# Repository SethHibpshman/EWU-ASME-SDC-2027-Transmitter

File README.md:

# EWU ASME SDC 2027 Transmitter

> A custom handheld Operator Console for the EWU ASME chapter's 2027 ASME Student Design Competition robot, built around an ESP32-S3 on a custom PCB and talking to the robot over ESP-NOW. **Work in progress.**

> This repo covers only the transmitter. The competition rules, playfield models, and the robot itself are in the main repo: [EWU-ASME-SDC-2027-Robot](https://github.com/SethHibpshman/EWU-ASME-SDC-2027-Robot).

## Table of Contents

- [Overview](#overview)
- [Status](#status)
- [Functionality](#functionality)
- [System Design](#system-design)
- [Bill of Materials](#bill-of-materials)
- [Author](#author)
- [AI Disclosure](#ai-disclosure)
- [License](#license)

## Overview

The 2027 ASME Student Design Competition (eFest SDC), PODIUM, has one robot compete in five Disciplines. Each Run starts with a 30-second autonomous phase and ends with a 2-minute crewed phase, where the team drives the robot through its own Operator Console. The rules allow exactly one control link on a license-free band, the robot must be able to be disabled from the remote, and any battery in the remote must be a commercially made cell.

Instead of reusing the hobby RC radio from the [2026 robot](https://github.com/SethHibpshman/EWU-ASME-SDC-2026-Robot), this project is a purpose-built controller: an ESP32-S3 dev board on a custom PCB with joysticks, potentiometers, buttons, a display, and its own rechargeable battery system. Reliability comes first, followed by learning C/C++, building transferable skills, and a clean-looking design.

## Status

| Stage | State |
|---|---|
| Rev A PCB | Designed for JLCPCB assembly, not built (over $100 for two units) |
| Rev B PCB | Ordered, hand-assembled, and tested |
| Firmware | Not started |

## Functionality

### Inputs and Feedback

The layout follows a typical RC transmitter: two joysticks, two potentiometers, and eight buttons in two diamond clusters of four.

| Feature | Part |
|---|---|
| **Microcontroller** | ESP32-S3-DevKitC-1 N16R8 (dual USB-C) in female headers |
| **Drive inputs** | 2x 2-axis analog joysticks (YF16-FL7.2-B5KA, 5 kΩ) |
| **Proportional inputs** | 2x rotary potentiometers (RK09K1130AAU, 10 kΩ) |
| **Buttons** | 8x 12 mm action buttons and a power button |
| **Display** | 128x64 I2C OLED (HS13L03W2C01) |
| **Status lights** | 5 mm center LED and the devkit's built-in LED |
| **Expansion** | 2x5 header for spare GPIO |
| **Mounting** | 4 grounded M3 holes, one in each corner |

### Wireless Link

The transmitter uses ESP-NOW on 2.4 GHz, Espressif's connectionless peer-to-peer protocol. It needs no router, has millisecond-level latency, and gives two-way telemetry between the robot and the transmitter.

| Radio | Rough Range | Needs Infrastructure? | Power | Best For |
|---|---|---|---|---|
| Wi-Fi | Tens of metres | Router plus internet | Moderate to high | Dashboards, apps, cloud |
| **ESP-NOW** | Similar to Wi-Fi, more outdoors | None | Low | Board-to-board messaging |
| LoRa | Hundreds of metres to kilometres | LoRa module, gateway for LoRaWAN | Very low | Remote, sparse sensors |

LoRa's range isn't needed for a pilot a few metres from the board, and its small packets limit how fast data can be sent. Wi-Fi needs a router.

### Power

| Feature | Part |
|---|---|
| **Battery** | Single Li-ion cell |
| **Charger and 5 V boost** | IP5306-I2C |
| **Battery protection** | IP3005A, with a bypass jumper (R20) |
| **USB ESD protection** | USBLC6-2SC6 |
| **Backfeed blocking** | SS34 Schottky on the boost output |
| **Soft shutdown** | 2N7000 on the IP5306 KEY pin, driven by the MCU |
| **Fuel gauge** | 100 kΩ / 100 kΩ divider to an ADC pin |

The I2C version of the IP5306 was chosen so the MCU can turn off its auto-shutoff, which would otherwise cut power after 30 seconds of low current draw. Over I2C the MCU can also read charging state and battery level.

## System Design

### Hardware

The back of the board carries the author's maker's mark, the board name, date and revision, and the EWU insignia for the team behind the eFest project.

Designed in KiCad 10 as a two-sheet schematic: the [main sheet](/assets/schematic/schematic_main.svg) (ESP32-S3, inputs, display, and expansion header) and a [Battery Charging & Protection sheet](/assets/schematic/schematic_power.svg). All project files are in [`/hardware/kicad_project_files`](/hardware/kicad_project_files).

#### ESP32-S3 Development Board

- 100 nF and 10 µF capacitors on the 3V3 rail: the 100 nF handles fast logic switching spikes, the 10 µF covers radio transmit bursts (~250 mA) before the regulator catches up.
- 100 nF on each analog input forms an RC low-pass filter with the pot or joystick (cutoff ~637 Hz for the 10 kΩ pots, ~1.27 kHz for the 5 kΩ joysticks). User input passes through; the IP5306's ~500 kHz switching noise and 2.4 GHz radio noise are blocked.

#### Battery and Power Management

USB data and VIN pass through the USBLC6-2SC6 ESD protection IC. The USB+ and USB- traces are routed together at matched length.

The IP5306 circuit follows the manufacturer's I2C application schematic, with these changes:

- I2C pulled up to 3V3 instead of BATT+ to protect the MCU
- 100 kΩ / 100 kΩ fuel-gauge divider for a finer battery reading
- SS34 Schottky on VOUT to block backfeed when the devkit is on USB power
- 2N7000 on the KEY pin so the MCU can force a shutdown
- Flashlight LED removed and the exposed pad grounded
- INT routed through a jumper (R5) so its voltage can be checked before it reaches a GPIO

The IP3005A battery protection IC is set up as the manufacturer recommends, with an optional jumper (R20) from BAT- to Pack- to bypass it.

#### User Input and Feedback

The joysticks and pots run from 3V3 to GND. Buttons connect a GPIO to GND, with pull-ups handled in firmware.

#### Exposed Pins

Spare usable GPIO is broken out to a 2x5 header for future expansion.

#### PCB

| Property | Value |
|---|---|
| Size | 150 x 110 x 1.6 mm, 2 layers |
| Routing | Back copper vertical, front copper horizontal |
| 1 mm traces | +P, BAT-, VIN, SW, VOUT |
| 0.5 mm traces | +5V, +3V3 |
| 0.2 mm traces | Signals |
| Ground | Poured on both layers, stitched with vias every 5 mm (under λ/10 at 2.4 GHz) |
| Finishing | Islands removed, teardrops added |

#### Rev A to Rev B

Rev B was a cost-cutting revision, going from over $100 to about $50 for two transmitters (about $25 each).

- Dropped JLCPCB assembly. The board is now hand-soldered in-house.
- Swapped 0603 passives for 0805 and gave hard-to-reach parts (like the inductor) hand-solder footprints.
- Replaced the SMD USB-C port with a 1x4 header (VIN, GND, USB+, USB-) wired to the ESP32-S3's native USB, so a USB-C module can be added later.
- Added labeled test pads (VIN, +P, BAT-, 3V3, 5V0, INT, fuel gauge, IO8) and back-side silkscreen.

#### Assembly and Bring-Up

Assembly took about two hours, plus two hours of testing. SMD parts went on first, then through-hole. The devkit sits in female headers, so it stayed off the board while the power section was tested from a 3.7 V bench supply.

| Fault | Cause | Fix |
|---|---|---|
| Boost output 2 V instead of 5 V | IP5306 exposed pad not soldered to ground | Reflowed the pad from the back through the via with flux |
| No USB device through J2 | USB+ open between USBLC6 and GPIO20 | Resoldered the USBLC6 |

With both fixed, the boost reads 5 V, a cell charges from 4.0 V to 4.2 V on USB, and the board enumerates through J2. The battery protection IC was out of stock, so it was left off and bypassed with R20.

### Software

Firmware will be C++ on the Arduino-ESP32 core. As a fail-safe, the robot stops all operations if it stops receiving packets from the transmitter.

```
EWU-ASME-SDC-2027-Transmitter/
├── assets/
│   ├── pcb_render_front.png                     # 3D render of the PCB, front
│   ├── pcb_render_back.jpg                      # 3D render of the PCB, back
│   ├── pcb_assembled.jpg                        # Photo of the assembled Rev B board
│   └── schematic/                               # Schematic sheets (SVG) and section images
└── hardware/
    ├── kicad_project_files/
    │   ├── transmitter.kicad_pro                # KiCad project
    │   ├── transmitter.kicad_sch                # Main schematic sheet
    │   ├── Battery Charging & Protection.kicad_sch
    │   └── transmitter.kicad_pcb                # PCB layout
    └── fabrication/                             # JLCPCB outputs
        ├── gerber/                              # Gerbers and drill files
        └── production_files/                    # BOM, CPL, and Gerber zip
```

## Bill of Materials

The full BOM with LCSC part numbers is in [`BOM-transmitter.csv`](/hardware/fabrication/production_files/BOM-transmitter.csv). Rev B costs about $25 per transmitter, with a minimum PCB order of 5.

## Author

**Seth Hibpshman**  
Student of Electrical Engineering, Eastern Washington University

## AI Disclosure
_AI (LLM) tools were used in the drafting and editing of this README._

## License

[GNU General Public License v3.0](LICENSE)

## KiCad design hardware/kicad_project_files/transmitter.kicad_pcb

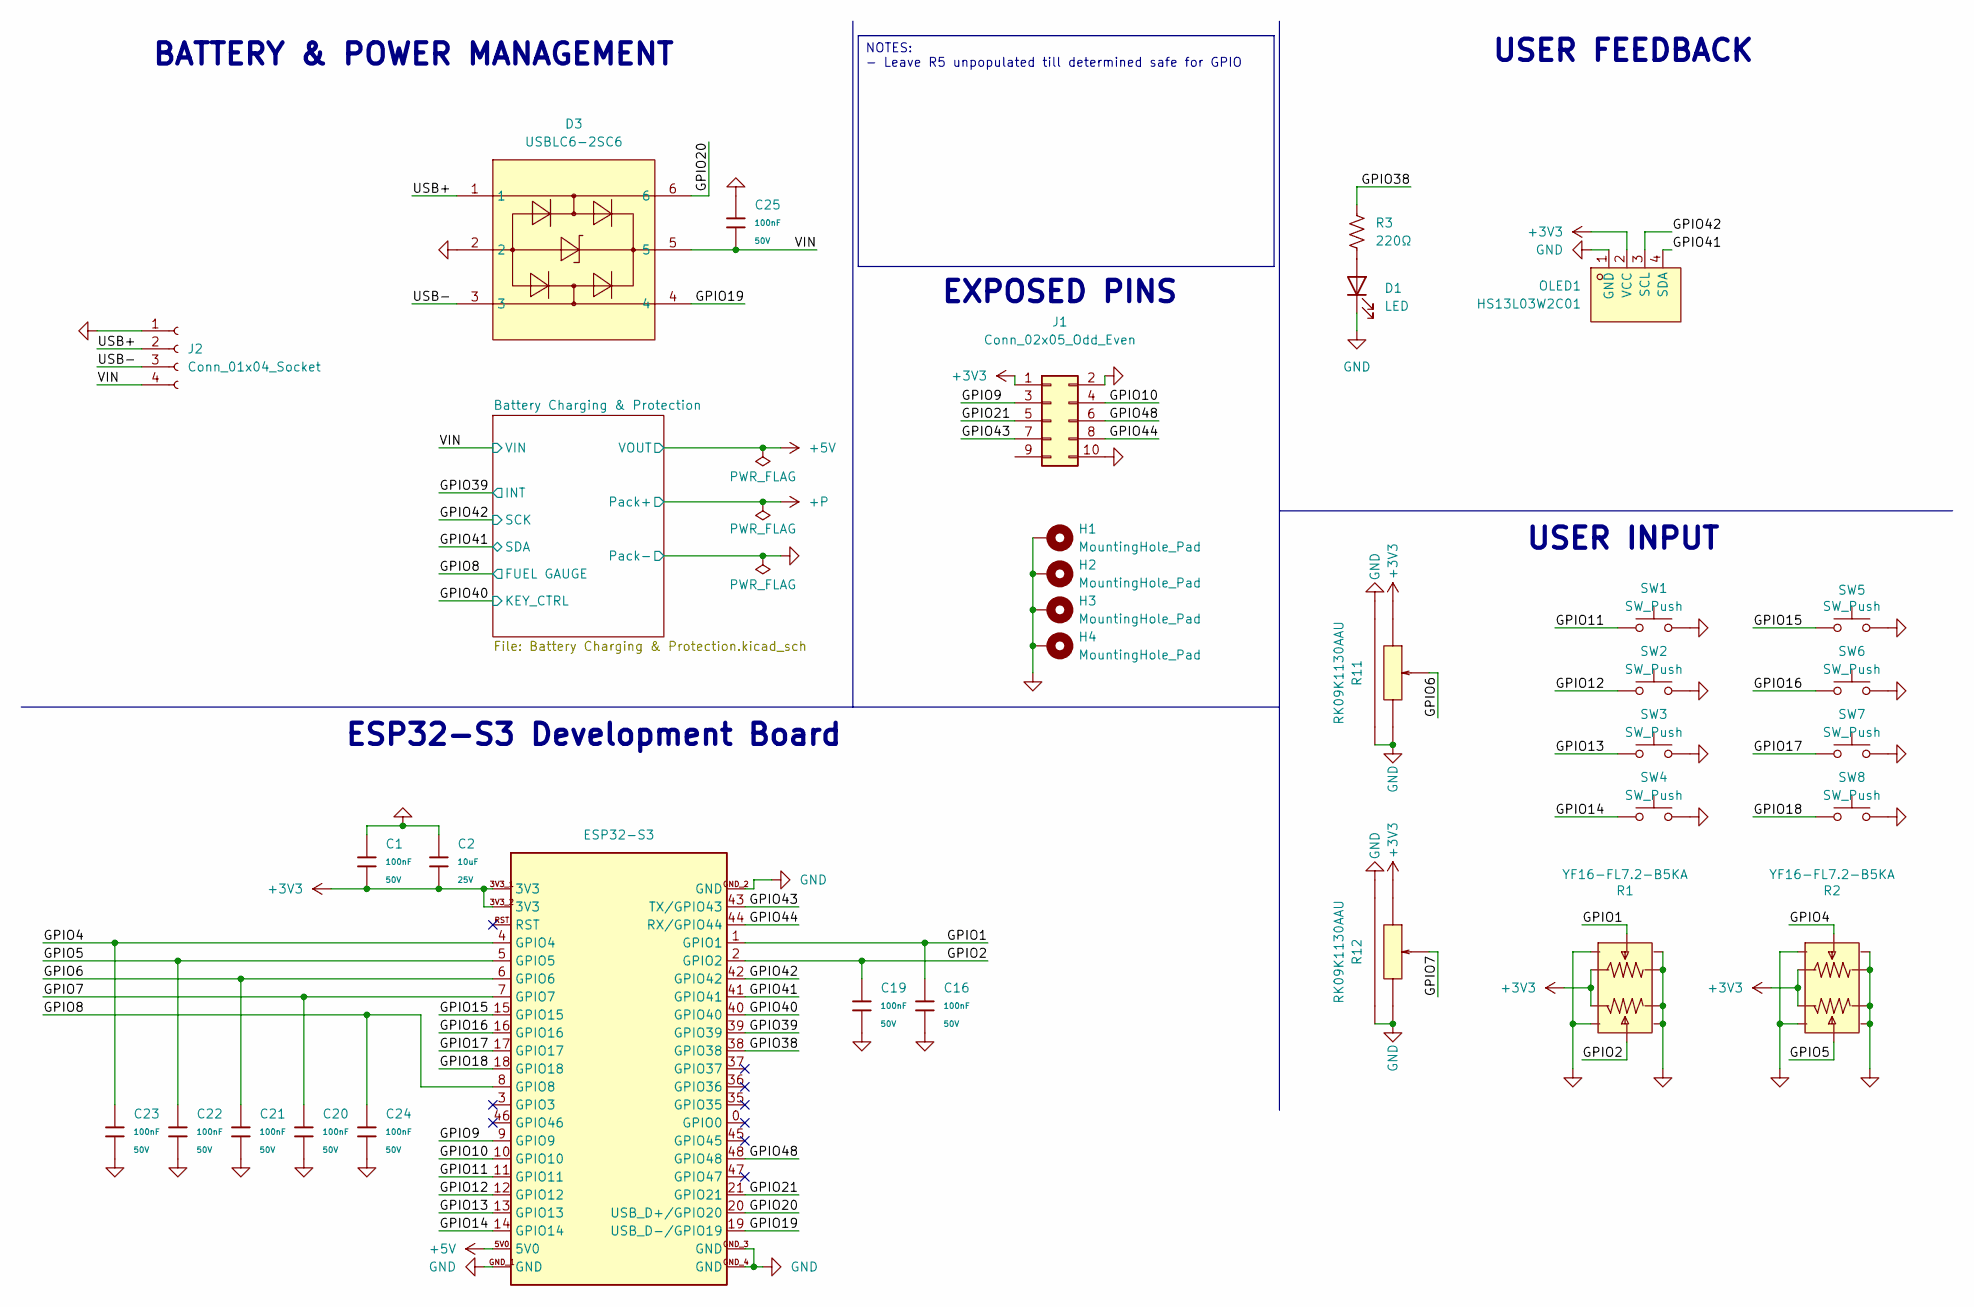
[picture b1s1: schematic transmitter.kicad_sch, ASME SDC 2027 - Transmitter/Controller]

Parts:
C1, C16, C19, C20, C21, C22, C23, C24, C25: 100nF; C_0805; Voltage Rated 50V; Tolerance ±10%; Part CC0603KRX7R9BB104; LCSC C14663
C2: 10uF; C_0805; Voltage Rated 25V; Tolerance ±20%; Part CL10A106MA8NRNC; LCSC C96446
D1: LED; LED_D5.0mm
D3: USBLC6-2SC6; SOT-23-6_L2.9-W1.6-P0.95-LS2.8-BL; MPN USBLC6-2SC6; LCSC Part C7519
ESP32-S3: Devboard_ESP32-S3_N16R8_DualUSB-C_YELUFT
H1, H2, H3, H4: MountingHole_Pad; MountingHole_3mm_Pad_Via
J1: Conn_02x05_Odd_Even; PinSocket_2x05_P2.54mm_Vertical
J2: Conn_01x04_Socket; PinHeader_1x04_P2.54mm_Vertical
OLED1: HS13L03W2C01; OLED-TH_L35.4-W33.5_HS13L03W2C01; MPN HS13L03W2C01; LCSC Part C7465997
R1, R2: YF16-FL7.2-B5KA; JOYTICK-TH_YF16-DFL7.2-B5KO-45-10-B5KO-55--RG-A22; MPN YF16-FL7.2-B5Ka(45-10)-R-A28; LCSC Part C37323739
R3: 220Ω; R_0805
R11, R12: RK09K1130AAU; RES-TH_RK09K1130AAU; MPN RK09K1130AAU; LCSC Part C202373
SW1, SW2, SW3, SW4, SW5, SW6, SW7, SW8: SW_Push; SW_PUSH-12mm_Wuerth-430476085716

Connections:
+3V3: C1.2, C2.2, ESP32-S3.3V3_1 (3V3), ESP32-S3.3V3_2 (3V3), J1.1, OLED1.2 (VCC), R1.3, R1.6, R2.3, R2.6, R11.3, R12.3; also elsewhere on the board
+5V: ESP32-S3.5V0; also elsewhere on the board
/GPIO1: C16.1, ESP32-S3.1 (GPIO1), R1.2
/GPIO2: C19.1, ESP32-S3.2 (GPIO2), R1.5
/GPIO4: C23.1, ESP32-S3.4 (GPIO4), R2.2
/GPIO5: C22.1, ESP32-S3.5 (GPIO5), R2.5
/GPIO6: C21.1, ESP32-S3.6 (GPIO6), R11.2
/GPIO7: C20.1, ESP32-S3.7 (GPIO7), R12.2
/GPIO8: C24.1, ESP32-S3.8 (GPIO8); also elsewhere on the board
/GPIO9: ESP32-S3.9 (GPIO9), J1.3
/GPIO10: ESP32-S3.10 (GPIO10), J1.4
/GPIO11: ESP32-S3.11 (GPIO11), SW1.1
/GPIO12: ESP32-S3.12 (GPIO12), SW2.1
/GPIO13: ESP32-S3.13 (GPIO13), SW3.1
/GPIO14: ESP32-S3.14 (GPIO14), SW4.1
/GPIO15: ESP32-S3.15 (GPIO15), SW5.1
/GPIO16: ESP32-S3.16 (GPIO16), SW6.1
/GPIO17: ESP32-S3.17 (GPIO17), SW7.1
/GPIO18: ESP32-S3.18 (GPIO18), SW8.1
/GPIO19: D3.4, ESP32-S3.19 (USB_D-/GPIO19)
/GPIO20: D3.6, ESP32-S3.20 (USB_D+/GPIO20)
/GPIO21: ESP32-S3.21 (GPIO21), J1.5
/GPIO38: ESP32-S3.38 (GPIO38), R3.1
/GPIO39: ESP32-S3.39 (GPIO39); also elsewhere on the board
/GPIO40: ESP32-S3.40 (GPIO40); also elsewhere on the board
/GPIO41: ESP32-S3.41 (GPIO41), OLED1.4 (SDA); also elsewhere on the board
/GPIO42: ESP32-S3.42 (GPIO42), OLED1.3 (SCL); also elsewhere on the board
/GPIO43: ESP32-S3.43 (TX/GPIO43), J1.7
/GPIO44: ESP32-S3.44 (RX/GPIO44), J1.8
/GPIO48: ESP32-S3.48 (GPIO48), J1.6
/USB+: D3.1, J2.2
/USB-: D3.3, J2.3
/VIN: C25.2, D3.5, J2.4; also elsewhere on the board
GND: C1.1, C2.1, C16.2, C19.2, C20.2, C21.2, C22.2, C23.2, C24.2, C25.1, D1.1 (K), D3.2, ESP32-S3.GND_1 (GND), ESP32-S3.GND_2 (GND), ESP32-S3.GND_3 (GND), ESP32-S3.GND_4 (GND), H1.1 (1_1), H2.1 (1_1), H3.1 (1_1), H4.1 (1_1), J1.2, J1.10, J2.1, OLED1.1 (GND), R1.1, R1.4, R1.7 (shell), R1.8 (shell), R1.9 (shell), R1.10 (shell), R2.1, R2.4, R2.7 (shell), R2.8 (shell), R2.9 (shell), R2.10 (shell), R11.1, R11.4 (EH), R11.5 (EH), R12.1, R12.4 (EH), R12.5 (EH), SW1.2, SW2.2, SW3.2, SW4.2, SW5.2, SW6.2, SW7.2, SW8.2; also elsewhere on the board
unnamed: D1.2 (A), R3.2

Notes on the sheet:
BATTERY & POWER MANAGEMENT
USER FEEDBACK
ESP32-S3 Development Board
USER INPUT
EXPOSED PINS
NOTES: - Leave R5 unpopulated till determined safe for GPIO

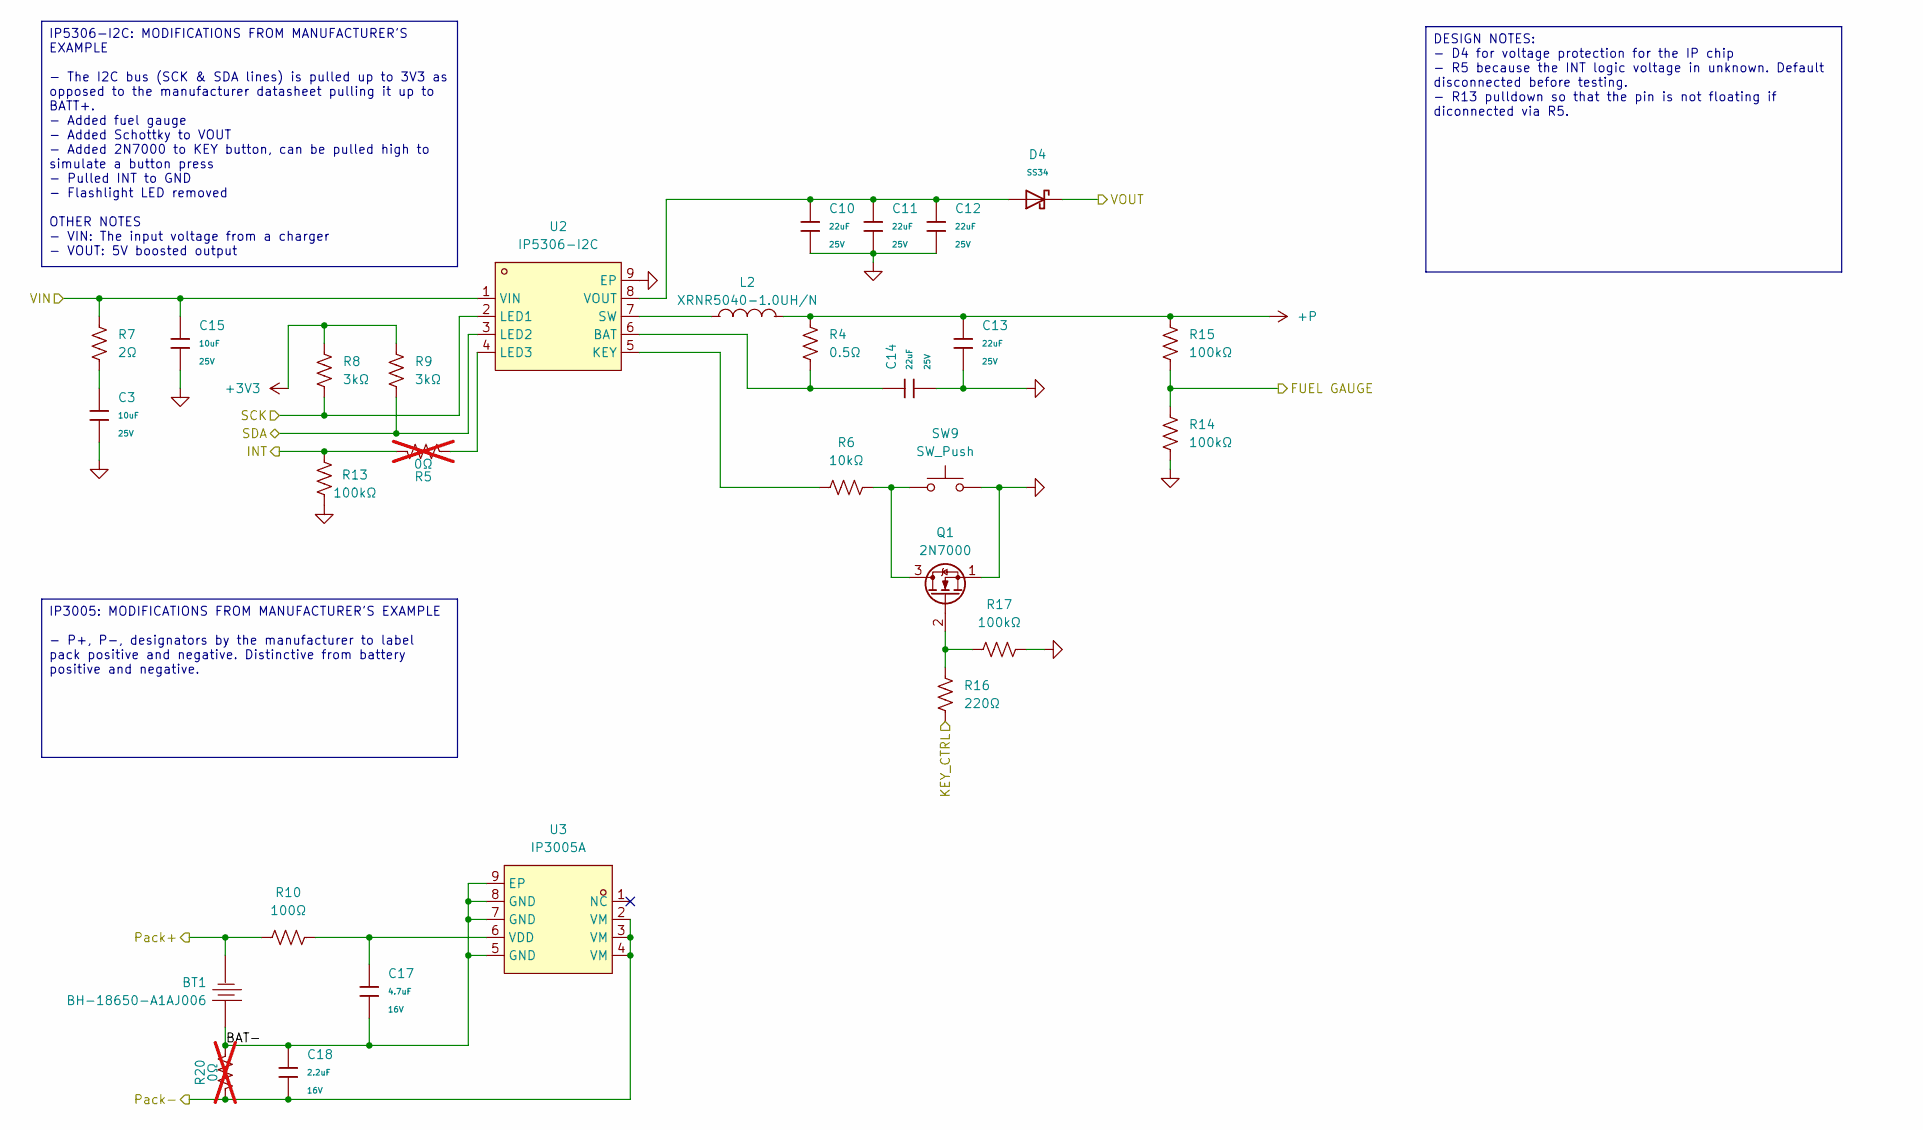
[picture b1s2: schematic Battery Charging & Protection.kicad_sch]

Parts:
BT1: BH-18650-A1AJ006; PinHeader_1x02_P2.54mm_Vertical; MPN BH-18650-A1AJ006; LCSC Part C5290175
C3, C15: 10uF; C_0805; Voltage Rated 25V; Tolerance ±20%; Part CL10A106MA8NRNC; LCSC C96446
C10, C11, C12, C13, C14: 22uF; C_0805; Voltage Rated 25V; Tolerance ±20%; Part CL21A226MAQNNNE; LCSC C45783
C17: 4.7uF; C_0805; Voltage Rated 16V; Tolerance ±10%; Part CL10A475KO8NNNC; LCSC C19666
C18: 2.2uF; C_0805; Voltage Rated 16V; Tolerance ±10%; Part CL10A225KO8NNNC; LCSC C23630
D4: SS34; D_SMA; Forward Voltage (Vf@If) 550mV@3A; Reverse Voltage (Vr) 40V; Part SS34; LCSC C8678
L2: XRNR5040-1.0UH/N; L_Taiyo-Yuden_NR-50xx_HandSoldering; MPN XRNR5040-1.0uH/N; LCSC Part C5339700
Q1: 2N7000; TO-92_Inline
R4: 0.5Ω; R_0805
R5: 0Ω; R_0805; not fitted
R6: 10kΩ; R_0805
R7: 2Ω; R_0805
R8, R9: 3kΩ; R_0805
R10: 100Ω; R_0805
R13, R14, R15, R17: 100kΩ; R_0805
R16: 220Ω; R_0805
R20: 0Ω; R_1206; not fitted
SW9: SW_Push; SW_PUSH-12mm_Wuerth-430476085716
U2: IP5306-I2C; ESOP-8_L4.9-W3.9-P1.27-LS6.0-BL-EP2.0; MPN IP5306-I2C; LCSC Part C488349
U3: IP3005A; ESOP-8_L4.9-W3.9-P1.27-LS6.0-BL-EP; MPN IP3005A; LCSC Part C181685

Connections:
+3V3: R8.1, R9.1; also elsewhere on the board
+5V: D4.1; also elsewhere on the board
+P: BT1.1, C13.1, L2.2, R4.1, R10.1, R15.1; also elsewhere on the board
/Battery Charging & Protection/BAT-: BT1.2, C17.2, C18.1, R20.1, U3.5 (GND), U3.7 (GND), U3.8 (GND), U3.9 (EP); also elsewhere on the board
/GPIO8: R14.1, R15.2; also elsewhere on the board
/GPIO39: R5.1, R13.1; also elsewhere on the board
/GPIO40: R16.1; also elsewhere on the board
/GPIO41: R9.2, U2.3 (LED2); also elsewhere on the board
/GPIO42: R8.2, U2.2 (LED1); also elsewhere on the board
/VIN: C15.1, R7.1, U2.1 (VIN); also elsewhere on the board
GND: C3.2, C10.2, C11.2, C12.2, C13.2, C14.2, C15.2, C18.2, Q1.1 (S), R13.2, R14.2, R17.1, R20.2, SW9.2, U2.9 (EP), U3.2 (VM), U3.3 (VM), U3.4 (VM); also elsewhere on the board
unnamed: C3.1, R7.2
unnamed: Q1.3 (D), R6.2, SW9.1
unnamed: Q1.2 (G), R16.2, R17.2
unnamed: C14.1, R4.2, U2.6 (BAT)
unnamed: R6.1, U2.5 (KEY)
unnamed 42: R5.2, U2.4 (LED3); also elsewhere on the board
unnamed: L2.1, U2.7 (SW)
unnamed: C10.1, C11.1, C12.1, D4.2, U2.8 (VOUT)
unnamed: C17.1, R10.2, U3.6 (VDD)

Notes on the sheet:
DESIGN NOTES: - D4 for voltage protection for the IP chip - R5 because the INT logic voltage in unknown. Default disconnected before testing. - R13 pulldown so that the pin is not floating if diconnected via R5.
IP5306-I2C: MODIFICATIONS FROM MANUFACTURER'S EXAMPLE - The I2C bus (SCK & SDA lines) is pulled up to 3V3 as opposed to the manufacturer datasheet pulling it up to BATT+. - Added fuel gauge - Added Schottky to VOUT - Added 2N7000 to KEY button, can be pulled high to simulate a button press - Pulled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
IP3005: MODIFICATIONS FROM MANUFACTURER'S EXAMPLE - P+, P-, designators by the manufacturer to label pack positive and negative. Distinctive from battery positive and negative.

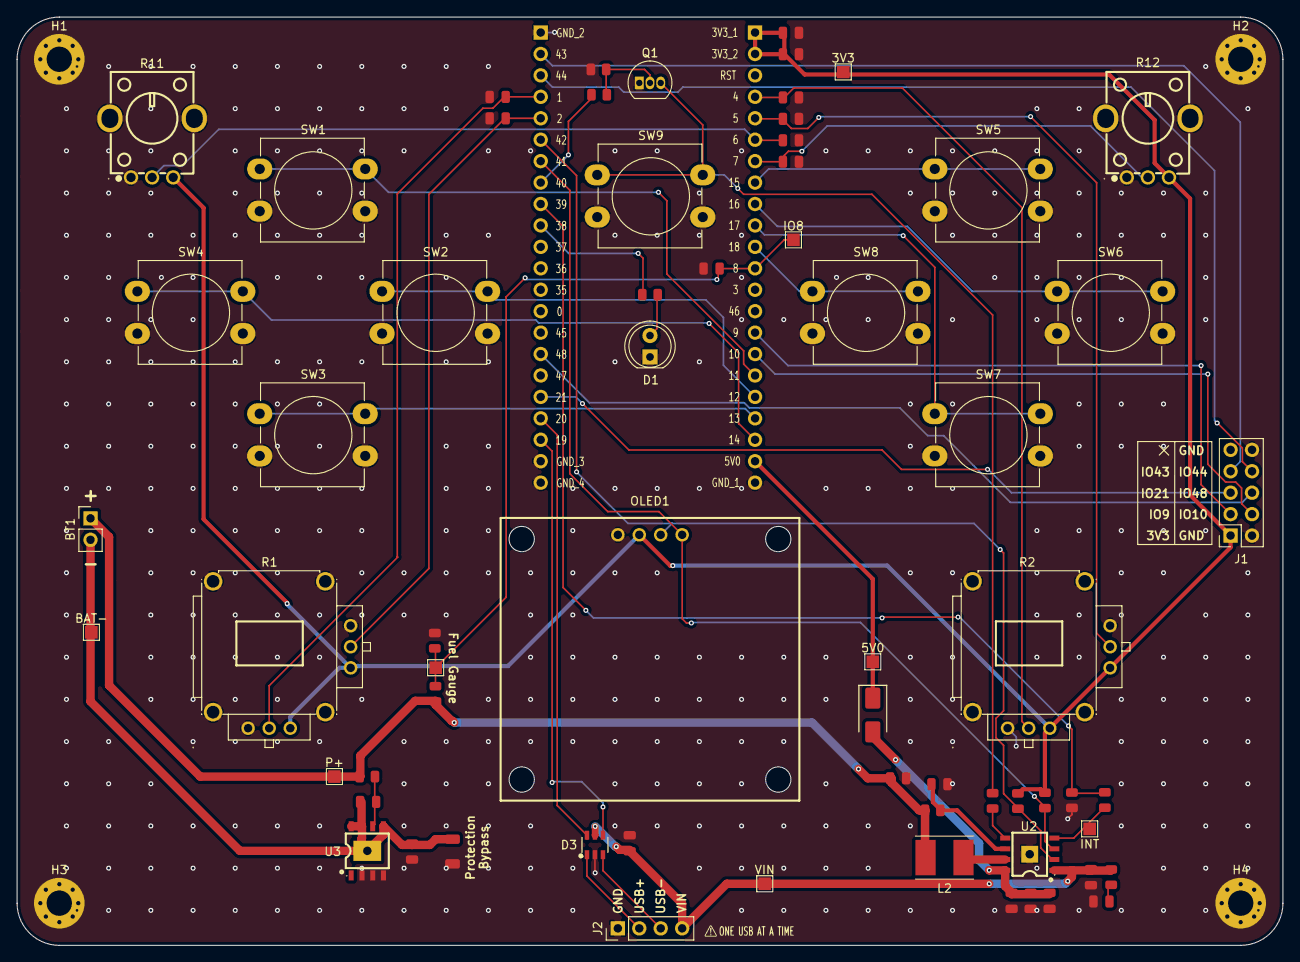
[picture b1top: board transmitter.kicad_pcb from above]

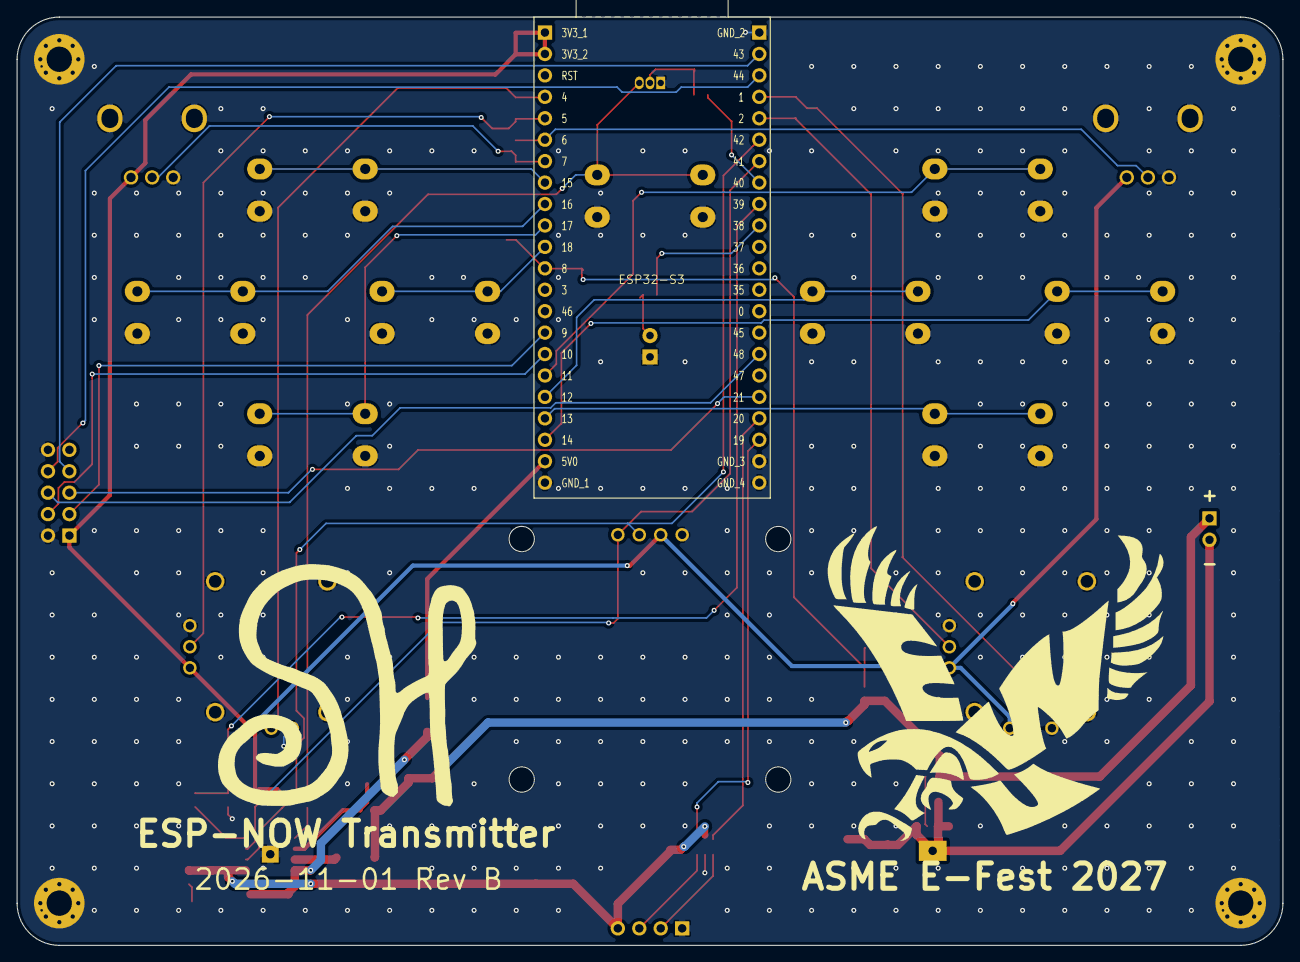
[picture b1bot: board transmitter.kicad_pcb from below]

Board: 2 copper layers, 150.0 x 110.0 mm, 73 parts (3 on the bottom side), 46 nets.

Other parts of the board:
3V3, 5V0: TestPoint_Pad_1.5x1.5mm
@1: Danger Triangle; LOGO
@2: Seth's Maker Mark; LOGO
@3: EWU Logo; LOGO
BAT-: TestPoint_Pad_1.5x1.5mm
FUELGAUGE_TEST: TestPoint_Pad_1.5x1.5mm
INT: TestPoint_Pad_1.5x1.5mm
IO8: TestPoint_Pad_1.5x1.5mm
P+: TestPoint_Pad_1.5x1.5mm
VIN: TestPoint_Pad_1.5x1.5mm

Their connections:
+3V3: 3V3.1; also elsewhere on the board
+5V: 5V0.1; also elsewhere on the board
+P: P+.1; also elsewhere on the board
/Battery Charging & Protection/BAT-: BAT-.1; also elsewhere on the board
/GPIO8: FUELGAUGE_TEST.1, IO8.1; also elsewhere on the board
/VIN: VIN.1; also elsewhere on the board
unnamed 42: INT.1; also elsewhere on the board

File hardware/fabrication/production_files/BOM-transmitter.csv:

Comment,Designator,Footprint,LCSC,Quantity
0.5Ω,R4,R_0805,C28319,1
100kΩ,"R13,R14,R15,R17",R_0805,C25611,4
100nF,"C1,C16,C19,C20,C21,C22,C23,C24,C25",C_0805,C49678,9
100Ω,R10,R_0805,C17408,1
10kΩ,R6,R_0805,C17414,1
10uF,"C15,C2,C3",C_0805,C15850,3
2.2uF,C18,C_0805,C377773,1
220Ω,"R16,R3",R_0805,C17557,2
22uF,"C10,C11,C12,C13,C14",C_0805,C45783,5
2N7000,Q1,TO-92_Inline,C9114,1
2Ω,R7,R_0805,C44051,1
3kΩ,"R8,R9",R_0805,C25633,2
4.7uF,C17,C_0805,C1779,1
HS13L03W2C01,OLED1,OLED-TH_L35.4-W33.5_HS13L03W2C01,C7465997,1
IP3005A,U3,ESOP-8_L4.9-W3.9-P1.27-LS6.0-BL-EP,C181685,1
IP5306-I2C,U2,ESOP-8_L4.9-W3.9-P1.27-LS6.0-BL-EP2.0,C488349,1
RK09K1130AAU,"R11,R12",RES-TH_RK09K1130AAU,C202373,2
SS34,D4,D_SMA,C8678,1
USBLC6-2SC6,D3,SOT-23-6_L2.9-W1.6-P0.95-LS2.8-BL,C7519,1
XRNR5040-1.0UH/N,L2,IND-SMD_L5.0-W5.0,C5339700,1
YF16-FL7.2-B5KA,"R1,R2",JOYTICK-TH_YF16-DFL7.2-B5KO-45-10-B5KO-55--RG-A22,C37323739,2
LED,D1,LED_D5.0mm,,1
~,ESP32-S3,Devboard_ESP32-S3_N16R8_DualUSB-C_YELUFT,,1
